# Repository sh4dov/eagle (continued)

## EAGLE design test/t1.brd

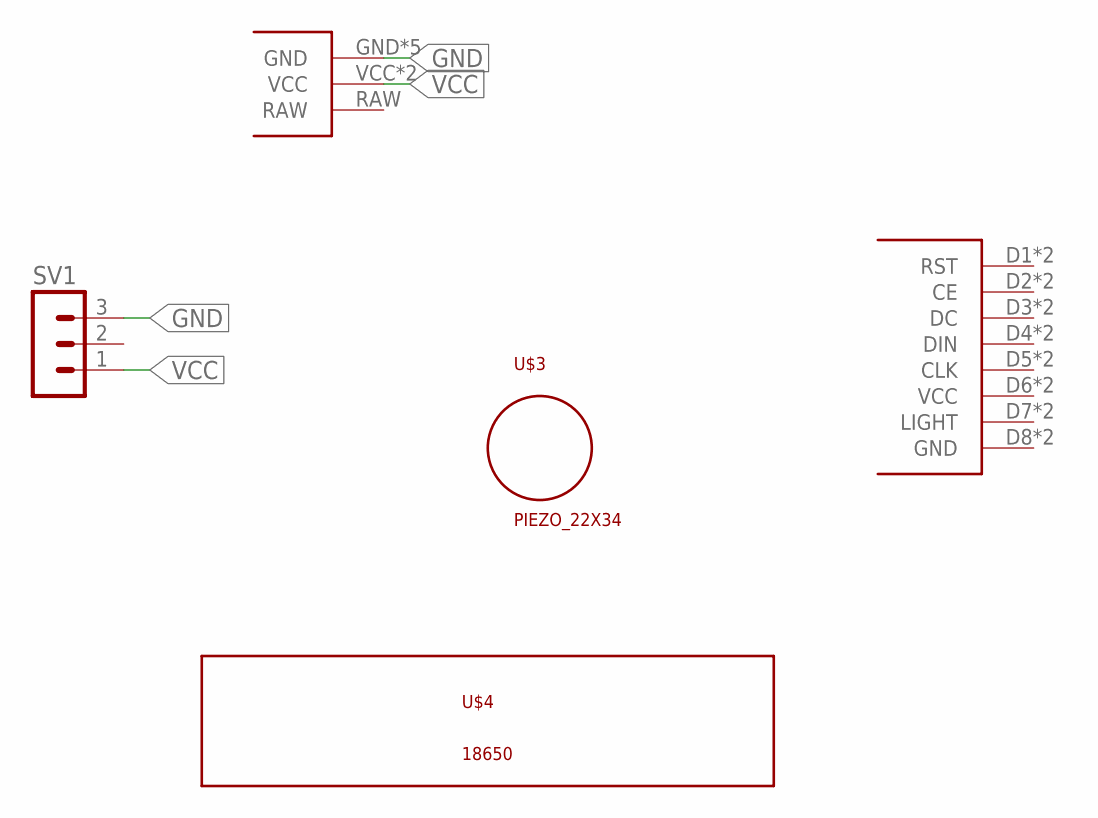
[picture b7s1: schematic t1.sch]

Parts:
SV1: MA03-1
U$1: PROMINI_V1
U$2: NOKIA_5110
U$3: PIEZO_22X34
U$4: 18650

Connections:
GND: SV1.3, U$1.GND, U$1.GND2 (GND), U$1.GND3 (GND), U$1.GND4 (GND), U$1.GND5 (GND)
VCC: SV1.1, U$1.VCC, U$1.VCC2 (VCC)

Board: 2 copper layers, 5 parts (0 on the bottom side), 2 nets, no tracks yet.

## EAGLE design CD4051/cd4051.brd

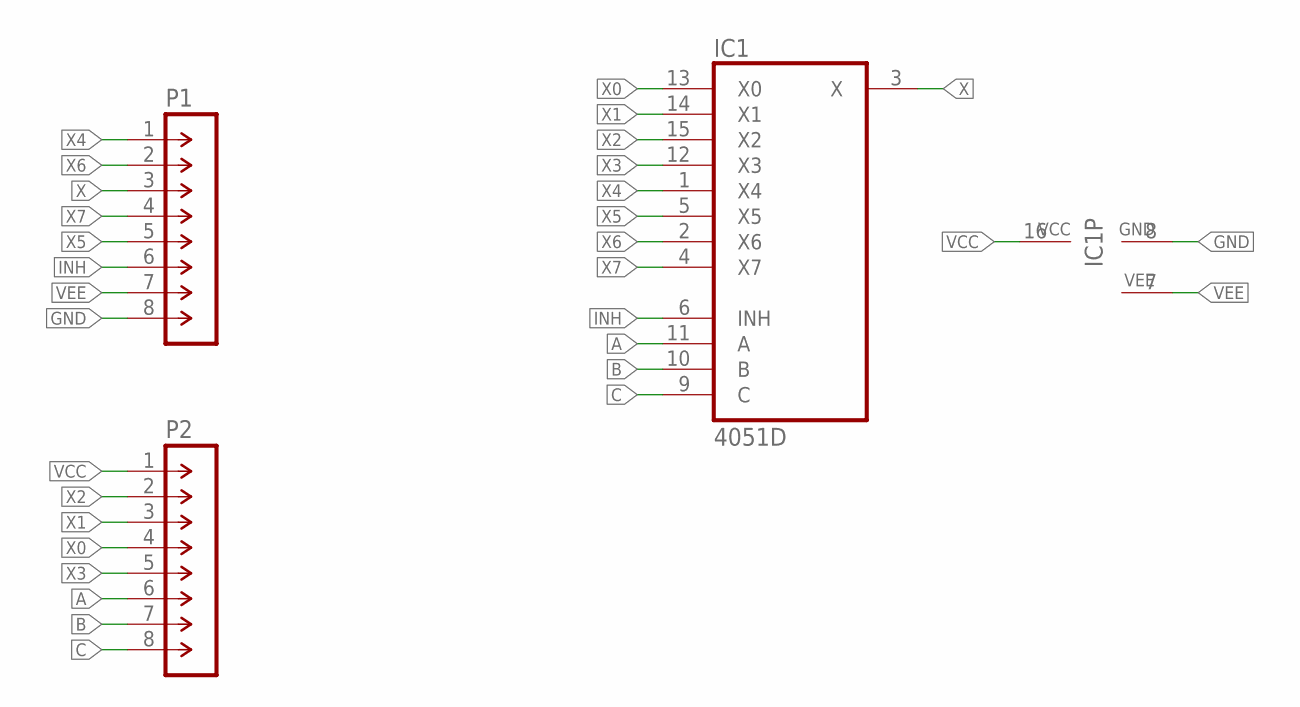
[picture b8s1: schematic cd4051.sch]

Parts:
IC1: 4051D; SO16
P1, P2: M-1X08-SIP-100-32Y; SIP-100-08-32Y

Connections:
A: IC1.11 (A), P2.6
B: IC1.10 (B), P2.7
C: IC1.9 (C), P2.8
GND: IC1.8 (GND), P1.8
INH: IC1.6 (INH), P1.6
VCC: IC1.16 (VCC), P2.1
VEE: IC1.7 (VEE), P1.7
X: IC1.3 (X), P1.3
X0: IC1.13 (X0), P2.4
X1: IC1.14 (X1), P2.3
X2: IC1.15 (X2), P2.2
X3: IC1.12 (X3), P2.5
X4: IC1.1 (X4), P1.1
X5: IC1.5 (X5), P1.5
X6: IC1.2 (X6), P1.2
X7: IC1.4 (X7), P1.4

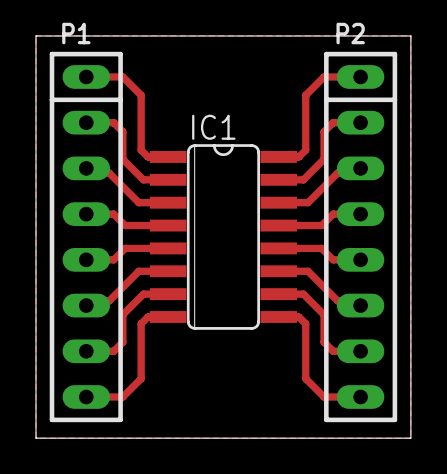
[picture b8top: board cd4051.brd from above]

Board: 2 copper layers, 20.8 x 22.3 mm, 3 parts (0 on the bottom side), 16 nets.

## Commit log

2016-01-25 initial
2016-03-20 UV box driver NiCd charger
2016-03-20 UV box for printing
2016-03-24 usb asp adapter
2016-03-28 Fixes to soldering.
2016-05-22 3.7 protect
2016-06-11 new update podlewacz v2
2016-07-14 new/update
2016-07-21 capacity measure sensor
2016-08-02 gas sensor
